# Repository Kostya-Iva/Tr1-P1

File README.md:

# Tr1-P1
Cartesian parallel manipulator, featuring "Tripteron" with 3 DoF, made as a student project for particular universitu course.
* Image of a robot:

# Motivation
The Tripteron project was born out of a practical need within the **EPIC** student research group: automating the preparation of metallographic specimens without breaking the bank.

Since professional, dedicated lab equipment is financially out of reach for most student budgets, this project delivers a cost-effective, simple to program, versatile alternative.

# Mechanical design

# Electronical design

# Programming
The system interfaces with three stepper motor drivers (X, Y, Z axes), dedicated limit switches (endstops) for homing, and control hardware.
The code architecture takes form of a state machine and it is described with this diagram:

Such architecture is described with one file, named: *stany.ino* written in the Arduino IDE for ESP32 DevBoard 

### Pin Mapping
| Component / Function | ESP32 Pin | Input / Output | Configuration / Description |
| :--- | :---: | :---: | :--- |
| **X-Axis STEP** | `GPIO22` | **OUTPUT** | Generates movement pulses for the X axis |
| **X-Axis DIR** | `GPIO23` | **OUTPUT** | Controls the direction of rotation for the X axis |
| **Y-Axis STEP** | `GPIO18` | **OUTPUT** | Generates movement pulses for the Y axis |
| **Y-Axis DIR** | `GPIO19` | **OUTPUT** | Controls the direction of rotation for the Y axis |
| **Z-Axis STEP** | `GPIO17` | **OUTPUT** | Generates movement pulses for the Z axis |
| **Z-Axis DIR** | `GPIO16` | **OUTPUT** | Controls the direction of rotation for the Z axis |
| **X-Axis Endstop** | `GPIO35` | **INPUT_PULLUP** | Limit switch for X home position |
| **Y-Axis Endstop** | `GPIO32` | **INPUT_PULLUP** | Limit switch for Y home position |
| **Z-Axis-bottom Endstop** | `GPIO33` | **INPUT_PULLUP** | Limit switch for Z home position |
| **Z-Axis-upper Endstop** | `GPIO25` | **INPUT_PULLUP** | Limit switch for Z home position |
| **START Button** | `GPIO14` | **INPUT_PULLUP** | Initiates the calibration and automation cycle |
| **STOP Button** | `GPIO12` | **INPUT_PULLUP** | Hardwired safety trigger for Emergency Stop |
---

#### State Descriptions:

* **`STATE_IDLE`** Remains stationary, actively polling the `START` button pin.
  
* **`STATE_HOMING`** Triggered after pressing START. Establishing the machine's absolute reference point.
  
* **`STATE_READY`** The homing was successfull. The parallel effector is calibrated at its home base, actively polling the `START` button pin.
  
* **`STATE_PROCESSING`** The system dynamically generates step pulses for all three axes simultaneously, executing predefined movement trajectory
  
* **`STATE_FINISHED`** The polishing cycle is complete. Retracts the effector away from the workpiece area, and transitions back to `STATE_IDLE` for the next run.

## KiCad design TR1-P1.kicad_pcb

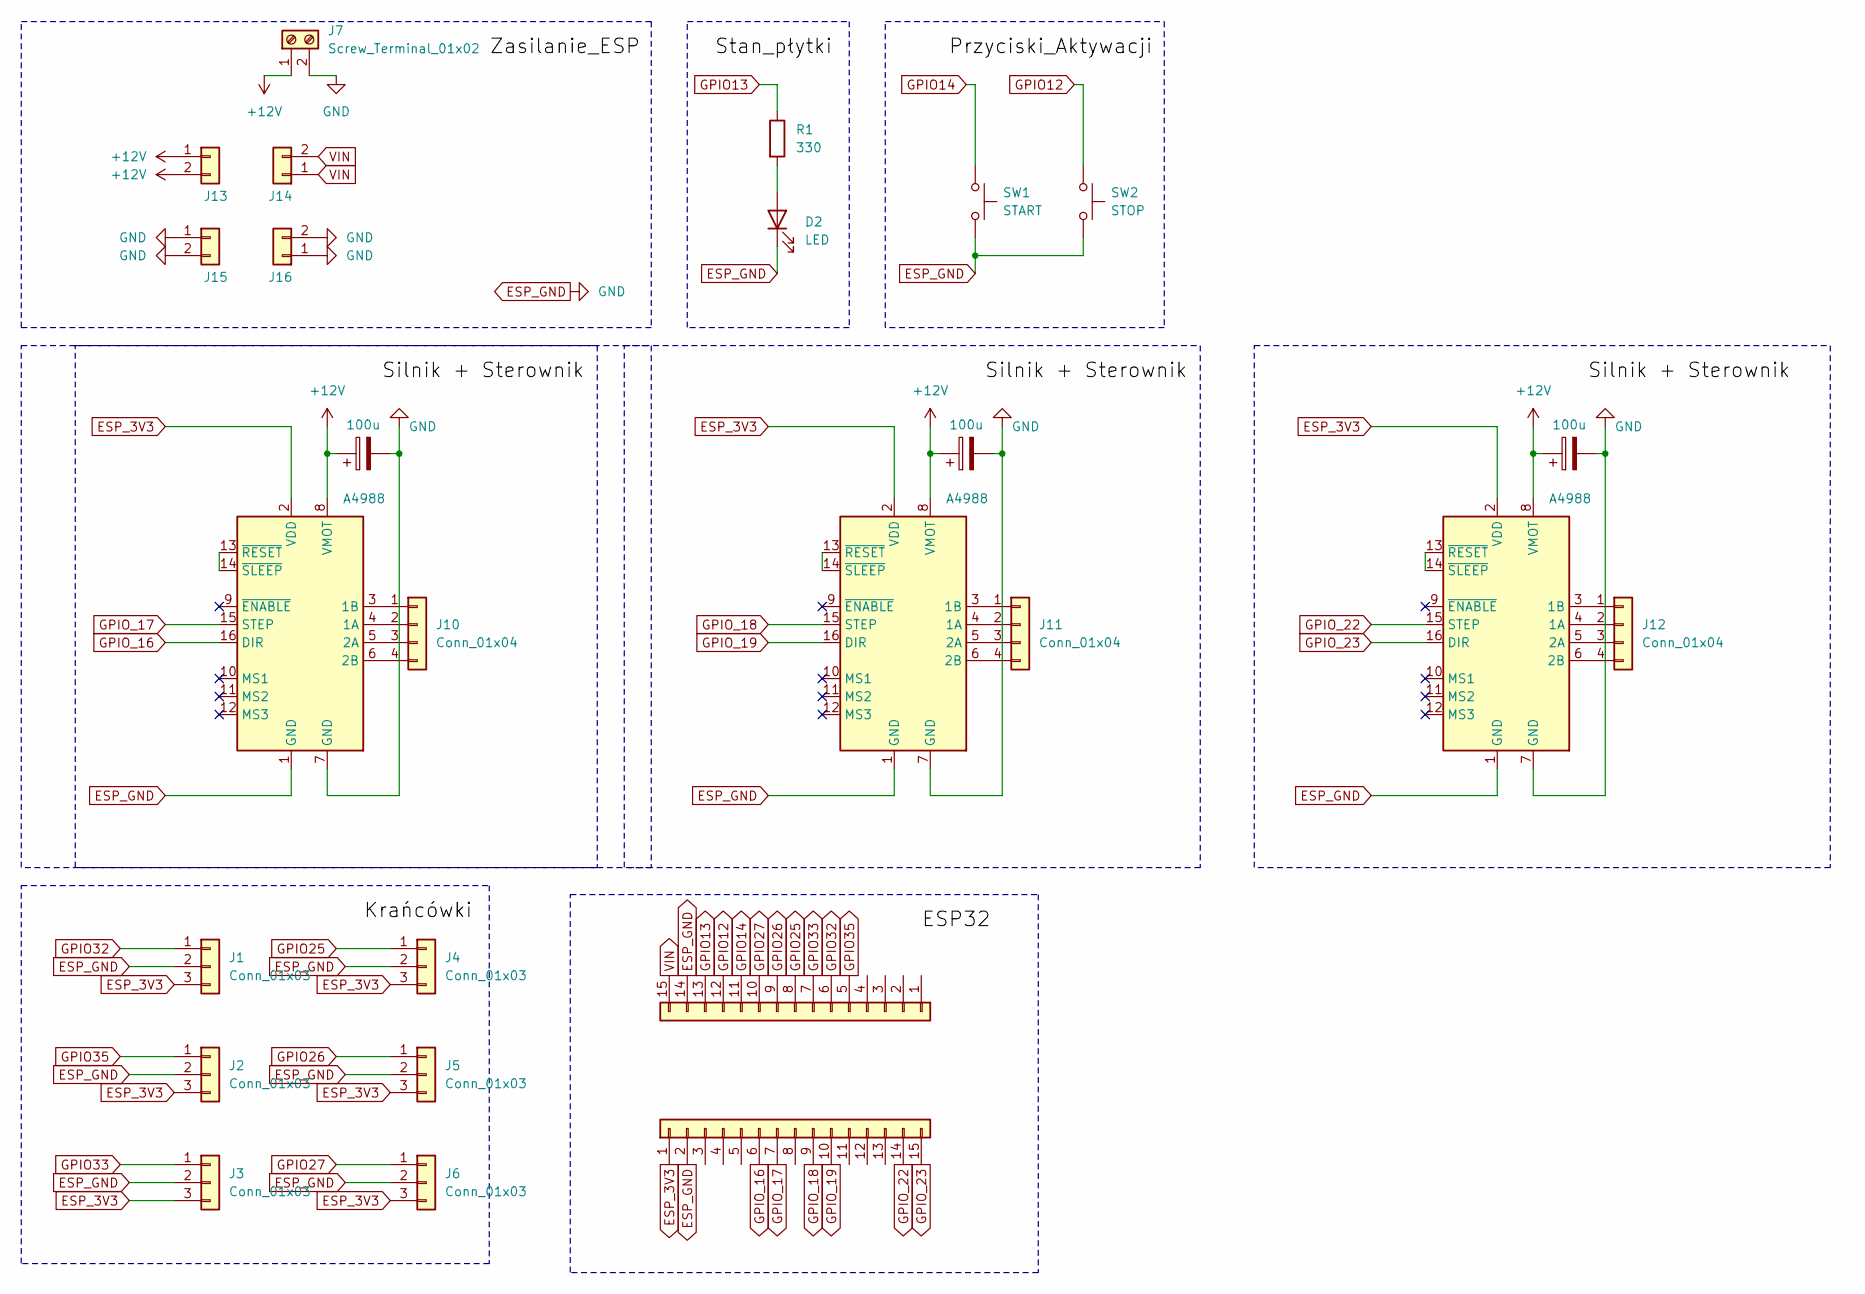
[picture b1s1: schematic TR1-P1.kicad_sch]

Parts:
A1, A2, A3: A4988; Pololu_Breakout-16_15.2x20.3mm
C3, C4, C5: 100u; CP_Radial_D5.0mm_P2.00mm
D2: LED; LED_D5.0mm
J1, J2, J3, J4, J5, J6: Conn_01x03; PinHeader_1x03_P2.54mm_Vertical
J7: Screw_Terminal_01x02; TerminalBlock_CUI_TB007-508-02_1x02_P5.08mm_Horizontal
J8, J9: Conn_01x15; PinSocket_1x15_P2.54mm_Vertical
J10, J11, J12: Conn_01x04; PinHeader_1x04_P2.54mm_Vertical
J13, J14, J15, J16: Conn_01x02; PinSocket_1x02_P2.54mm_Vertical
R1: 330; R_Axial_DIN0207_L6.3mm_D2.5mm_P7.62mm_Horizontal
SW1: START; SW_PUSH-12mm
SW2: STOP; SW_PUSH-12mm

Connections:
+12V: A1.8 (VMOT), A2.8 (VMOT), A3.8 (VMOT), C3.1, C4.1, C5.1, J7.1, J13.1, J13.2
ESP_3V3: A1.2 (VDD), A2.2 (VDD), A3.2 (VDD), J1.3, J2.3, J3.3, J4.3, J5.3, J6.3, J8.1
ESP_GND: A1.1 (GND), A1.7 (GND), A2.1 (GND), A2.7 (GND), A3.1 (GND), A3.7 (GND), C3.2, C4.2, C5.2, D2.1 (K), J1.2, J2.2, J3.2, J4.2, J5.2, J6.2, J7.2, J8.2, J9.14, J15.1, J15.2, J16.1, J16.2, SW1.2, SW2.2
GPIO12: J9.12, SW2.1
GPIO13: J9.13, R1.1
GPIO14: J9.11, SW1.1
GPIO25: J4.1, J9.8
GPIO26: J5.1, J9.9
GPIO27: J6.1, J9.10
GPIO32: J1.1, J9.6
GPIO33: J3.1, J9.7
GPIO35: J2.1, J9.5
GPIO_16: A1.16 (DIR), J8.6
GPIO_17: A1.15 (STEP), J8.7
GPIO_18: A2.15 (STEP), J8.9
GPIO_19: A2.16 (DIR), J8.10
GPIO_22: A3.15 (STEP), J8.14
GPIO_23: A3.16 (DIR), J8.15
unnamed: A1.4 (1A), J10.2
unnamed: A1.3 (1B), J10.1
unnamed: A1.5 (2A), J10.3
unnamed: A1.6 (2B), J10.4
unnamed: A1.13 (~RESET), A1.14 (~SLEEP)
unnamed: A2.4 (1A), J11.2
unnamed: A2.3 (1B), J11.1
unnamed: A2.5 (2A), J11.3
unnamed: A2.6 (2B), J11.4
unnamed: A2.13 (~RESET), A2.14 (~SLEEP)
unnamed: A3.4 (1A), J12.2
unnamed: A3.3 (1B), J12.1
unnamed: A3.5 (2A), J12.3
unnamed: A3.6 (2B), J12.4
unnamed: A3.13 (~RESET), A3.14 (~SLEEP)
unnamed: D2.2 (A), R1.2
VIN: J9.15, J14.1, J14.2

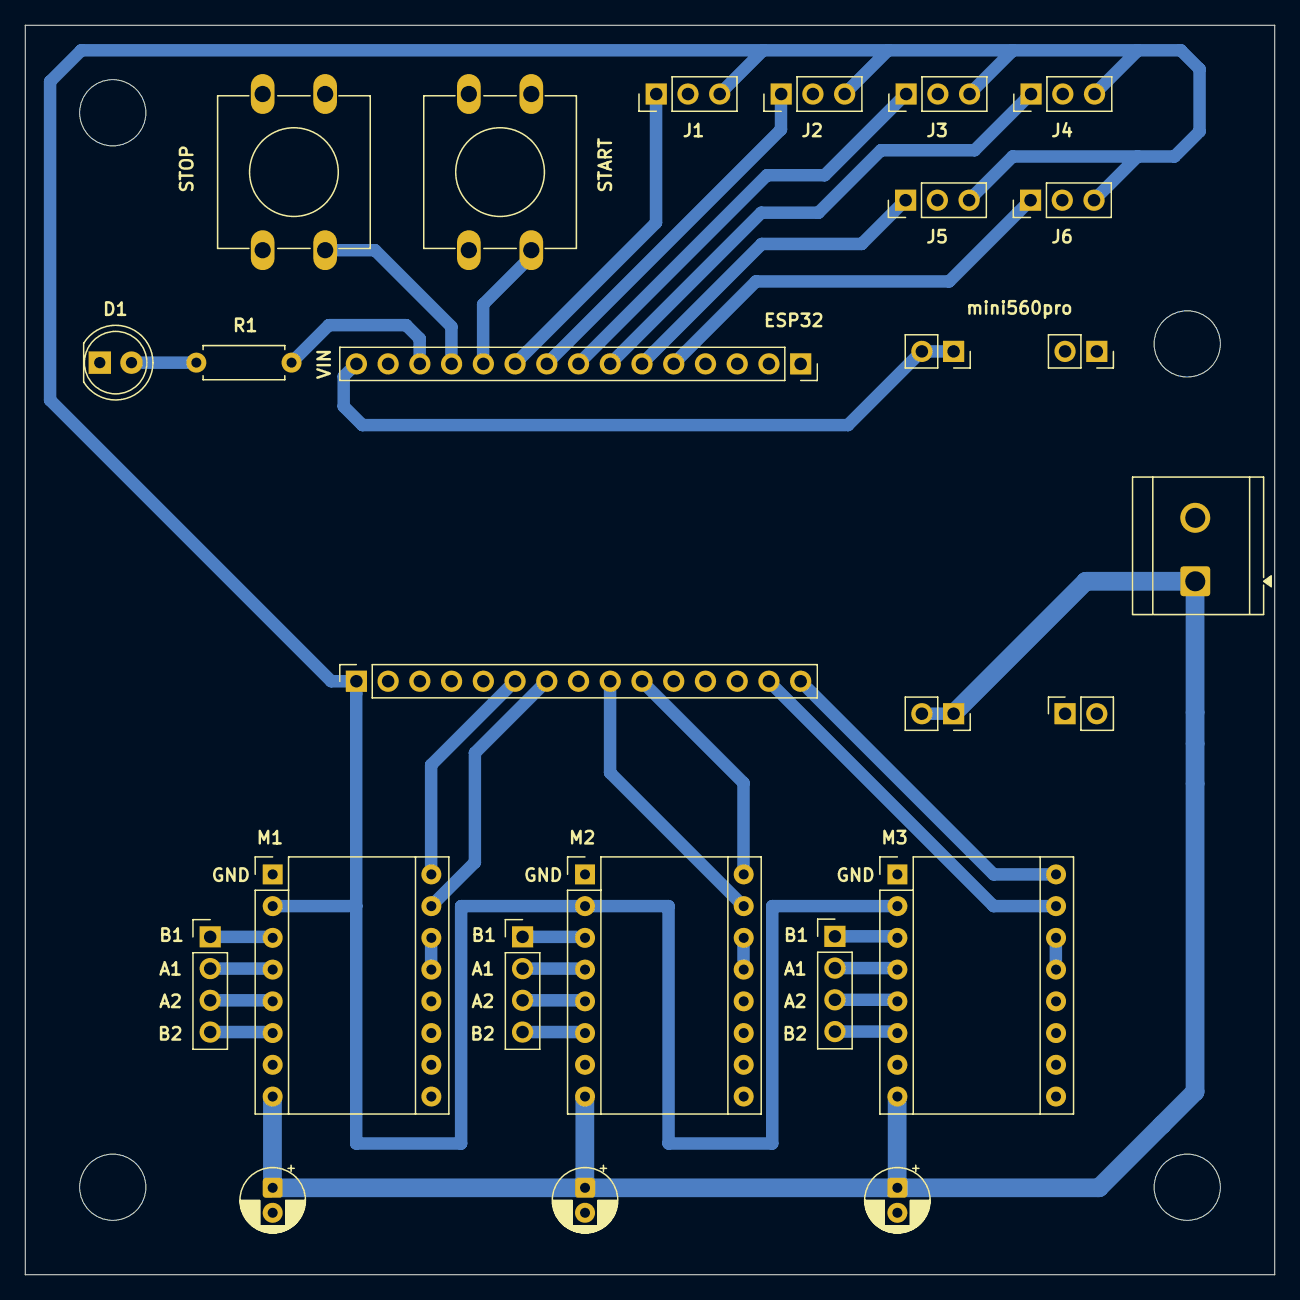
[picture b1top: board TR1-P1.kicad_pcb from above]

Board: 2 copper layers, 100.0 x 100.0 mm, 26 parts (0 on the bottom side), 35 nets.

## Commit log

2026-06-07 Base code for the robot
    Code that makes robot move the end-effector by the desired trajectory (which currently is circle), whole structure is based on the state-machine for ESP32, written in the Arduino IDE
2026-06-07 State machine diagram
    Visualization of a working code for the manipulator
2026-06-07 Image of a robot that we made
2026-06-07 Enhance README with project details and motivation
    Expanded project description and added motivation for the Tripteron robot. Included an image reference and sections for mechanical, electronic, and programming design.
2026-06-07 Improve image display in README
    Updated image formatting in README.md for better alignment.
2026-06-07 State machine diagram
2026-06-07 Enhance README with system architecture and pin mapping
    Added detailed descriptions of the system's components, pin mapping, and state machine architecture.
2026-06-07 added docs
2026-06-07 Refine state descriptions in README.md
    Updated descriptions for various states to improve clarity and conciseness.
